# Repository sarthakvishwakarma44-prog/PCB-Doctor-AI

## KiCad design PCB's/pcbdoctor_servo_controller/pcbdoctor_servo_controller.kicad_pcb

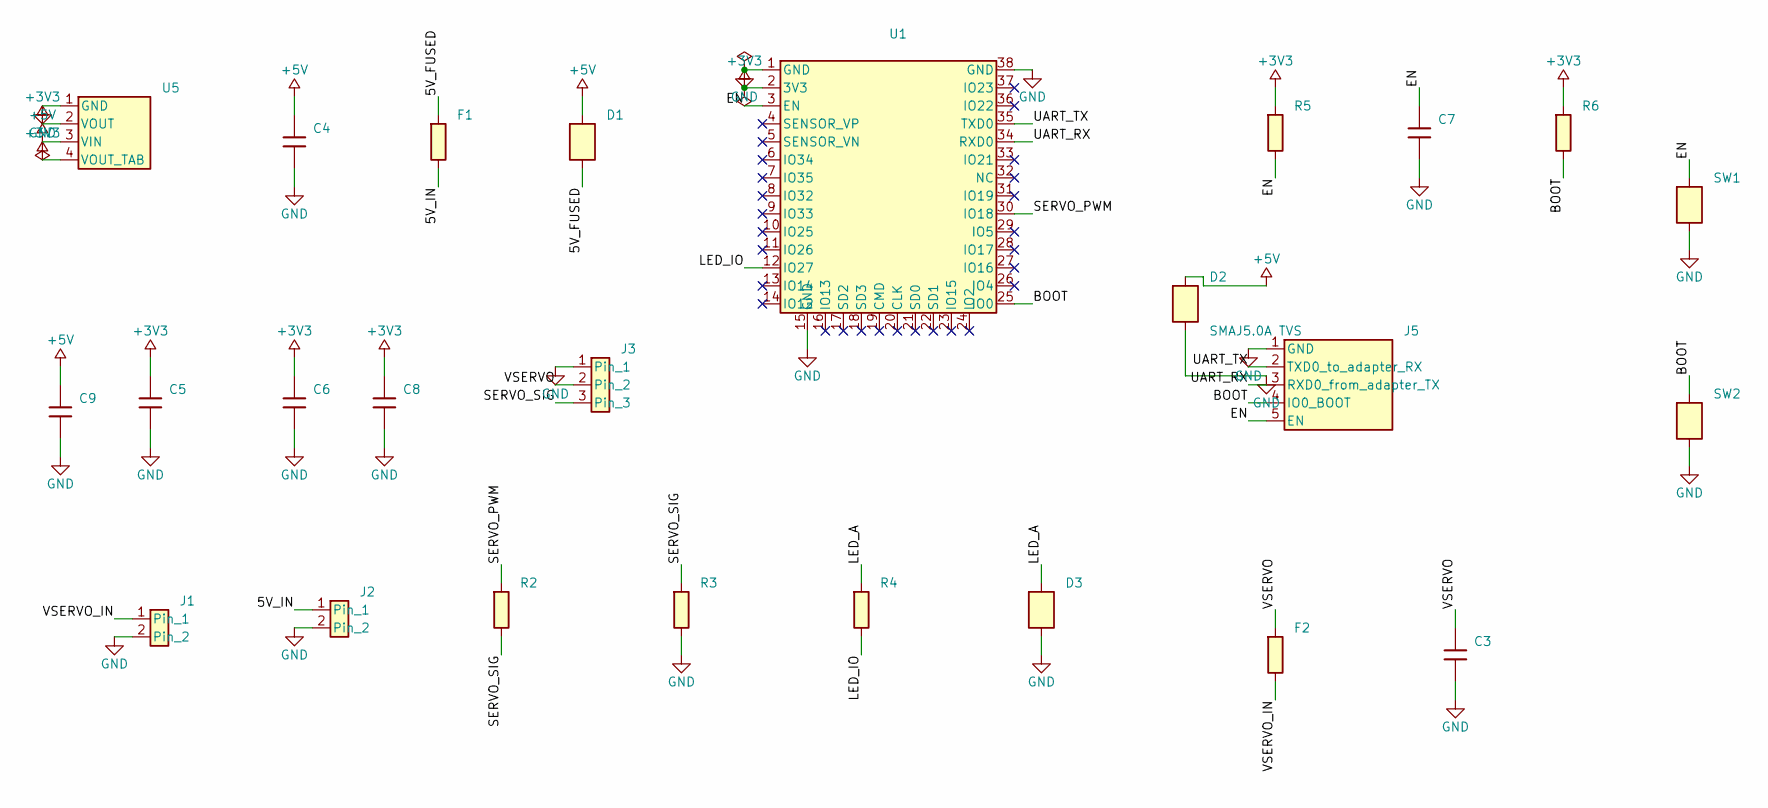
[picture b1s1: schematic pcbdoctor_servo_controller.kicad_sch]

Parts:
C3: 470uF (TBD by servo); CP_Radial_D8.0mm_P3.50mm
C4: 10uF 25V; C_0805
C5: 22uF tantalum; CP_Tantalum_A_3216
C6, C9: 10uF 10V; C_0805
C7: 1uF; C_0805
C8: 100nF; C_0805
D1: SS14; D_SMA
D2: SMAJ5.0A TVS; D_SMA
D3: STATUS; LED_D3.0mm
F1: PTC 1A (TBD); Fuse_1206
F2: FUSE (TBD by servo); Fuse_Radial_P5.08mm
J1: SERVO PWR IN; TerminalBlock_1x02_P5.08mm
J2: 5V LOGIC IN; TerminalBlock_1x02_P5.08mm
J3: SERVO GND/V+/SIG; PinHeader_1x03_P2.54mm
J5: UART programming; PinHeader_1x05_P2.54mm
R2: 330; R_0805
R3, R5, R6: 10k; R_0805
R4: 1k; R_0805
SW1: EN (reset); SW_Push_6mm
SW2: BOOT (IO0); SW_Push_6mm
U1: ESP32-WROOM-32E; ESP32_WROOM_32E_reconstructed
U5: AMS1117-3.3; SOT-223

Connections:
+3V3: C5.1, C6.1, C8.1, R5.1, R6.1, U1.2 (3V3), U5.2 (VOUT), U5.4 (VOUT_TAB)
+5V: C4.1, C9.1, D1.1 (K), D2.1 (K), U5.3 (VIN)
/5V_FUSED: D1.2 (A), F1.1
/5V_IN: F1.2, J2.1
/BOOT: J5.4 (IO0_BOOT), R6.2, SW2.1, U1.25 (IO0)
/EN: C7.1, J5.5 (EN), R5.2, SW1.1, U1.3 (EN)
/LED_A: D3.2 (A), R4.1
/LED_IO: R4.2, U1.12 (IO27)
/SERVO_PWM: R2.1, U1.30 (IO18)
/SERVO_SIG: J3.3, R2.2, R3.1
/UART_RX: J5.3 (RXD0_from_adapter_TX), U1.34 (RXD0)
/UART_TX: J5.2 (TXD0_to_adapter_RX), U1.35 (TXD0)
/VSERVO: C3.1, F2.1, J3.2
/VSERVO_IN: F2.2, J1.1
GND: C3.2, C4.2, C5.2, C6.2, C7.2, C8.2, C9.2, D2.2 (A), D3.1 (K), J1.2, J2.2, J3.1, J5.1 (GND), R3.2, SW1.2, SW2.2, U1.1 (GND), U1.15 (GND), U1.38 (GND), U5.1 (GND)

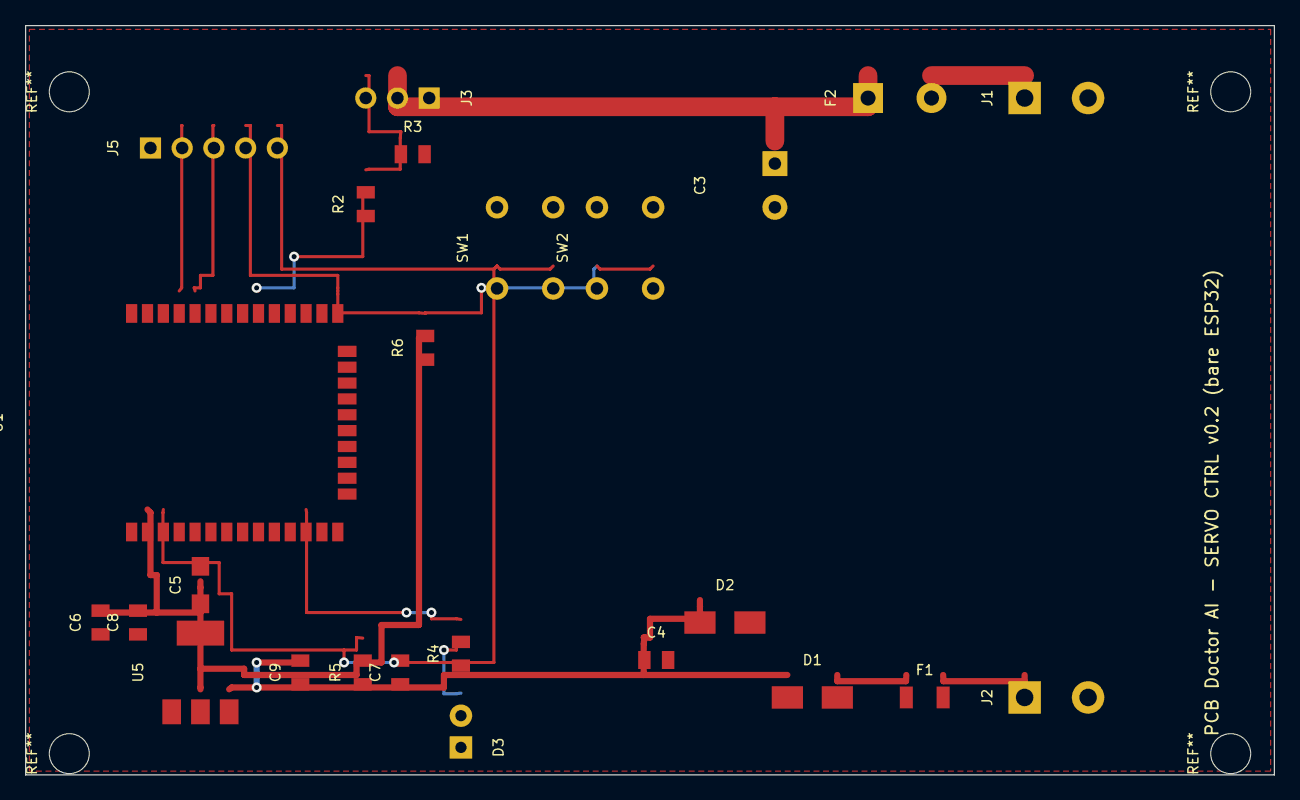
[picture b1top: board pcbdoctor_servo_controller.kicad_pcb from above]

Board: 2 copper layers, 100.0 x 60.0 mm, 25 parts (0 on the bottom side), 15 nets.

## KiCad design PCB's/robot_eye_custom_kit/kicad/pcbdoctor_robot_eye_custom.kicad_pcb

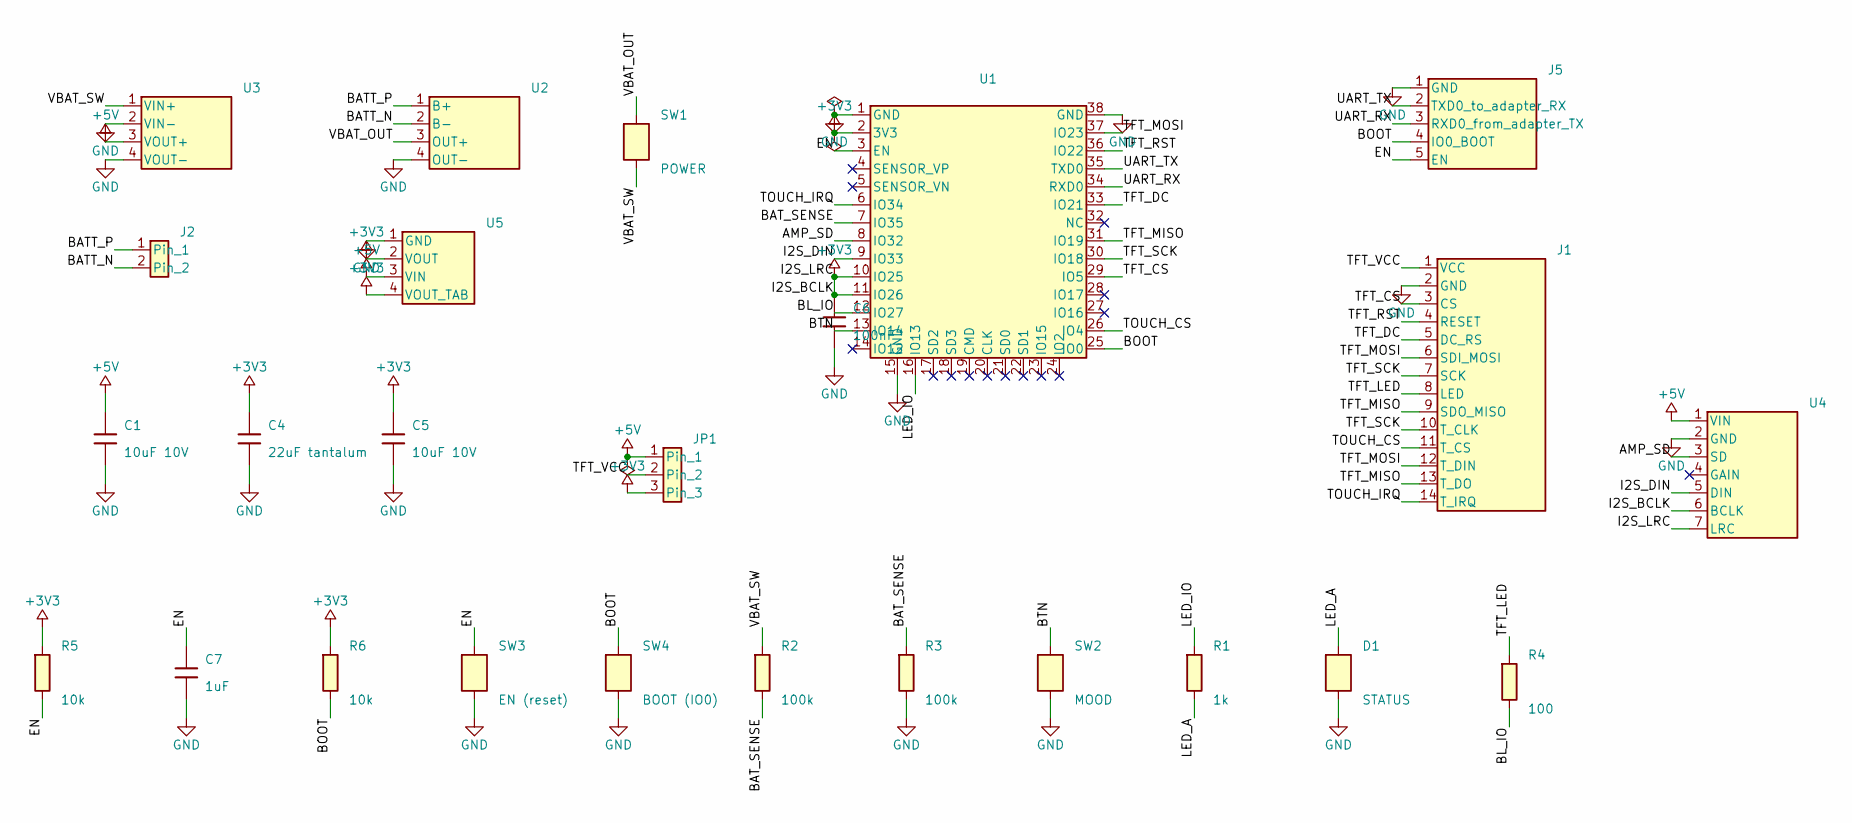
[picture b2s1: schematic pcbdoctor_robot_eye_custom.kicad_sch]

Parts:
C1, C5: 10uF 10V; C_0805
C4: 22uF tantalum; CP_Tantalum_A_3216
C6: 100nF; C_0805
C7: 1uF; C_0805
D1: STATUS; LED_D3.0mm
J1: ILI9486 3.5in SPI module; PinHeader_1x14_P2.54mm
J2: Li-ion battery; PinHeader_1x02_P2.54mm
J5: UART programming; PinHeader_1x05_P2.54mm
JP1: TFT VCC: 5V / 3V3 jumper; PinHeader_1x03_P2.54mm
R1: 1k; R_0805
R2, R3: 100k; R_0805
R4: 100; R_0805
R5, R6: 10k; R_0805
SW1: POWER; SW_Slide_2pad_P2.54
SW2: MOOD; SW_Push_6mm
SW3: EN (reset); SW_Push_6mm
SW4: BOOT (IO0); SW_Push_6mm
U1: ESP32-WROOM-32E; ESP32_WROOM_32E_reconstructed
U2: TP4056 USB-C charger+protection; PinHeader_1x04_P2.54mm
U3: MT3608 boost (set 5.0V first!); PinHeader_1x04_P2.54mm
U4: MAX98357A I2S amp -> speaker; PinHeader_1x07_P2.54mm
U5: AMS1117-3.3; SOT-223

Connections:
+3V3: C4.1, C5.1, C6.1, JP1.3, R5.1, R6.1, U1.2 (3V3), U1.10 (IO25), U1.11 (IO26), U4.6 (BCLK), U4.7 (LRC), U5.2 (VOUT), U5.4 (VOUT_TAB)
+5V: C1.1, JP1.1, U3.3 (VOUT+), U4.1 (VIN), U5.3 (VIN)
/AMP_SD: U1.8 (IO32), U4.3 (SD)
/BATT_N: J2.2, U2.2 (B-)
/BATT_P: J2.1, U2.1 (B+)
/BAT_SENSE: R2.2, R3.1, U1.7 (IO35)
/BL_IO: R4.2, U1.12 (IO27)
/BOOT: J5.4 (IO0_BOOT), R6.2, SW4.1, U1.25 (IO0)
/BTN: SW2.1, U1.13 (IO14)
/EN: C7.1, J5.5 (EN), R5.2, SW3.1, U1.3 (EN)
/I2S_DIN: U1.9 (IO33), U4.5 (DIN)
/LED_A: D1.2 (A), R1.2
/LED_IO: R1.1, U1.16 (IO13)
/TFT_CS: J1.3 (CS), U1.29 (IO5)
/TFT_DC: J1.5 (DC_RS), U1.33 (IO21)
/TFT_LED: J1.8 (LED), R4.1
/TFT_MISO: J1.9 (SDO_MISO), J1.13 (T_DO), U1.31 (IO19)
/TFT_MOSI: J1.6 (SDI_MOSI), J1.12 (T_DIN), U1.37 (IO23)
/TFT_RST: J1.4 (RESET), U1.36 (IO22)
/TFT_SCK: J1.7 (SCK), J1.10 (T_CLK), U1.30 (IO18)
/TFT_VCC: J1.1 (VCC), JP1.2
/TOUCH_CS: J1.11 (T_CS), U1.26 (IO4)
/TOUCH_IRQ: J1.14 (T_IRQ), U1.6 (IO34)
/UART_RX: J5.3 (RXD0_from_adapter_TX), U1.34 (RXD0)
/UART_TX: J5.2 (TXD0_to_adapter_RX), U1.35 (TXD0)
/VBAT_OUT: SW1.1, U2.3 (OUT+)
/VBAT_SW: R2.1, SW1.2, U3.1 (VIN+)
GND: C1.2, C4.2, C5.2, C6.2, C7.2, D1.1 (K), J1.2 (GND), J5.1 (GND), R3.2, SW2.2, SW3.2, SW4.2, U1.1 (GND), U1.15 (GND), U1.38 (GND), U2.4 (OUT-), U3.2 (VIN-), U3.4 (VOUT-), U4.2 (GND), U5.1 (GND)

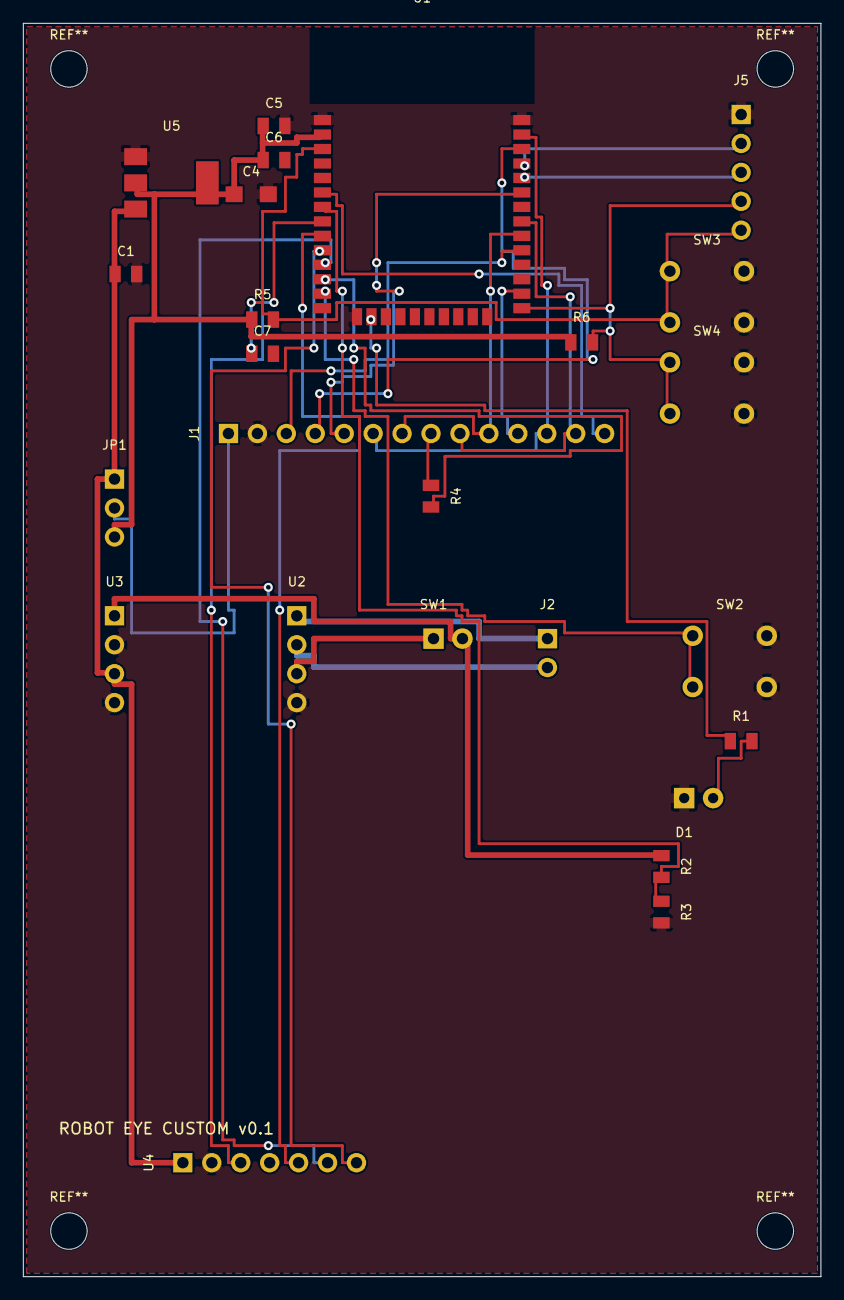
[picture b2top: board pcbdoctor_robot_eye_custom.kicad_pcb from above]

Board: 2 copper layers, 70.0 x 110.0 mm, 25 parts (0 on the bottom side), 28 nets.

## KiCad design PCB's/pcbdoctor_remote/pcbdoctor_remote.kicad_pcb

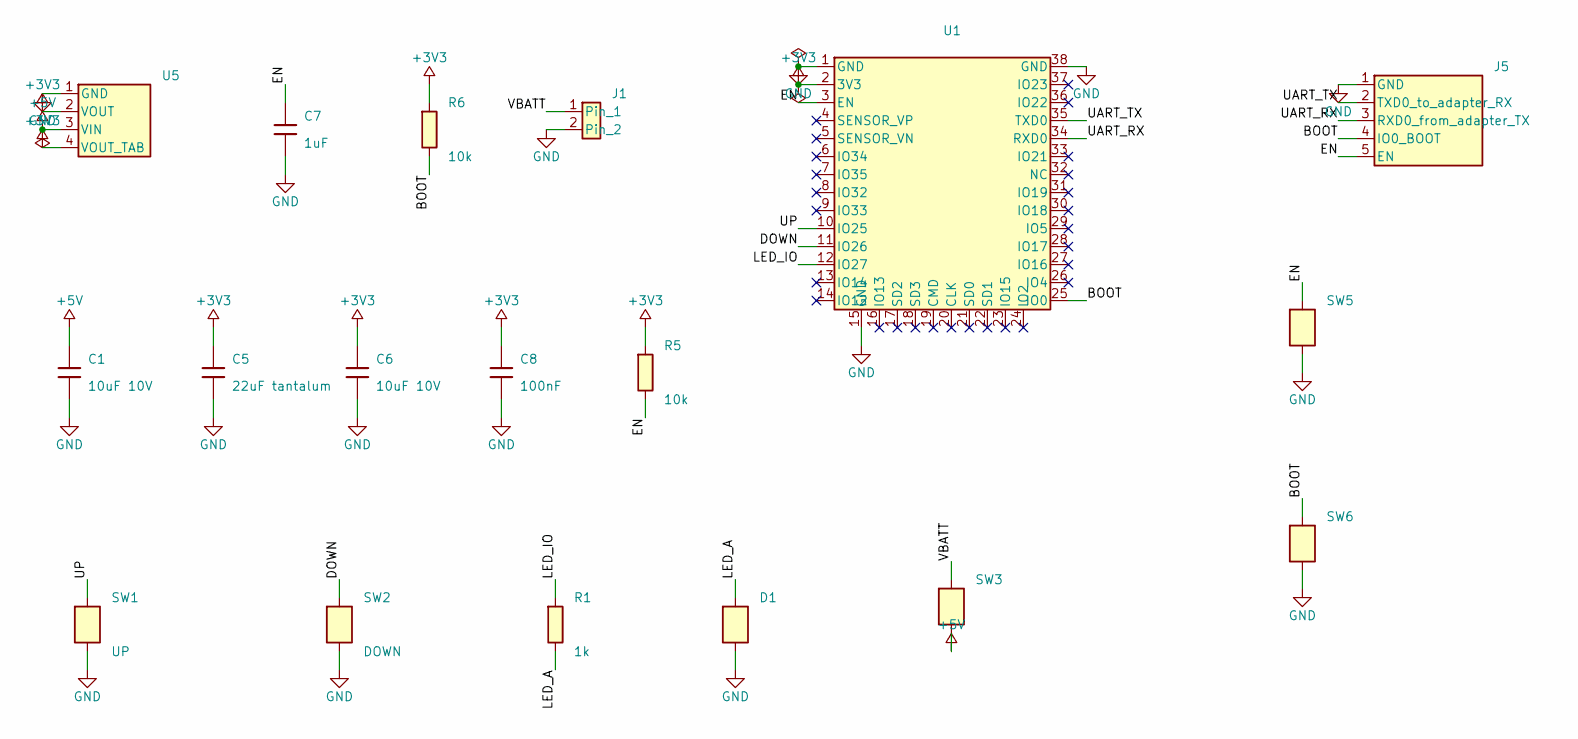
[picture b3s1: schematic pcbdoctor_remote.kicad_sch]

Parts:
C1, C6: 10uF 10V; C_0805
C5: 22uF tantalum; CP_Tantalum_A_3216
C7: 1uF; C_0805
C8: 100nF; C_0805
D1: STATUS; LED_D3.0mm
J1: 5V IN (regulated); PinHeader_1x02_P2.54mm
J5: UART programming; PinHeader_1x05_P2.54mm
R1: 1k; R_0805
R5, R6: 10k; R_0805
SW1: UP; SW_Push_6mm
SW2: DOWN; SW_Push_6mm
SW3: POWER; SW_Slide_2pad_P2.54
SW5: EN (reset); SW_Push_6mm
SW6: BOOT (IO0); SW_Push_6mm
U1: ESP32-WROOM-32E; ESP32_WROOM_32E_reconstructed
U5: AMS1117-3.3; SOT-223

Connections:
+3V3: C5.1, C6.1, C8.1, R5.1, R6.1, U1.2 (3V3), U5.2 (VOUT), U5.4 (VOUT_TAB)
+5V: C1.1, SW3.2, U5.3 (VIN)
/BOOT: J5.4 (IO0_BOOT), R6.2, SW6.1, U1.25 (IO0)
/DOWN: SW2.1, U1.11 (IO26)
/EN: C7.1, J5.5 (EN), R5.2, SW5.1, U1.3 (EN)
/LED_A: D1.2 (A), R1.2
/LED_IO: R1.1, U1.12 (IO27)
/UART_RX: J5.3 (RXD0_from_adapter_TX), U1.34 (RXD0)
/UART_TX: J5.2 (TXD0_to_adapter_RX), U1.35 (TXD0)
/UP: SW1.1, U1.10 (IO25)
/VBATT: J1.1, SW3.1
GND: C1.2, C5.2, C6.2, C7.2, C8.2, D1.1 (K), J1.2, J5.1 (GND), SW1.2, SW2.2, SW5.2, SW6.2, U1.1 (GND), U1.15 (GND), U1.38 (GND), U5.1 (GND)

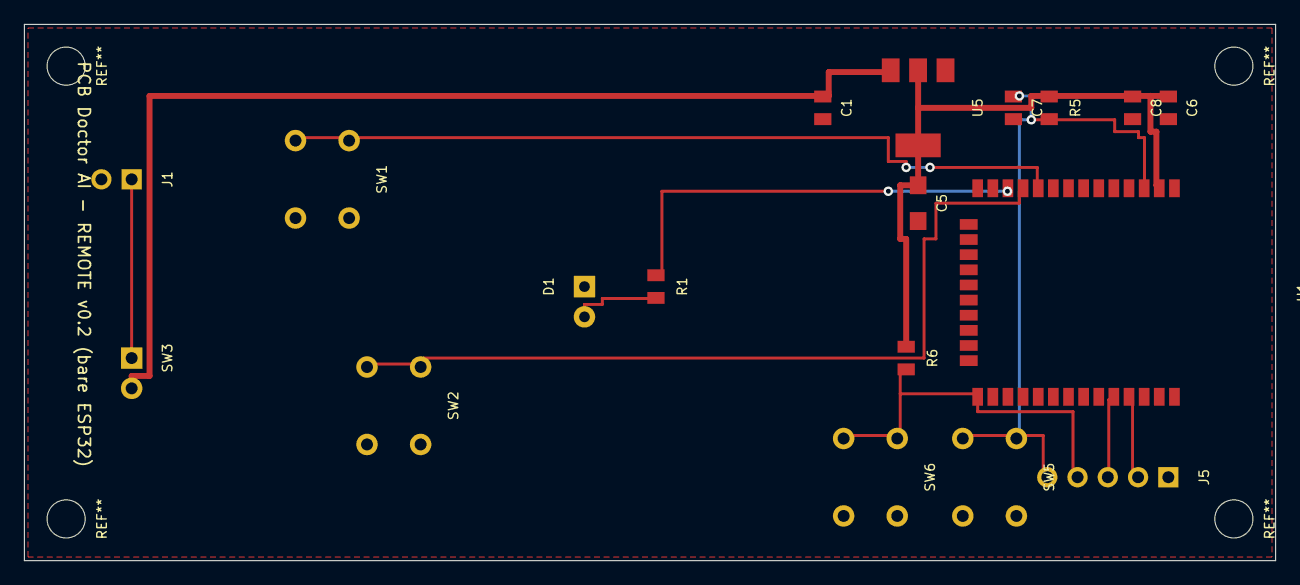
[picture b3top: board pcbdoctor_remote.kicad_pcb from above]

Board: 2 copper layers, 105.0 x 45.0 mm, 18 parts (0 on the bottom side), 12 nets.
